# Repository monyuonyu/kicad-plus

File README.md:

**English** | [日本語](README.ja.md) | [简体中文](README.zh-CN.md)

> Translated from [README.ja.md](README.ja.md) (the Japanese version is the original) at commit `fab6b11`.

# kicad-plus — an enhanced KiCad that can work on boards without a GUI

(Formerly **kicad-ja-plus**. The old command names `kicad-local`, `kicad-ja`, `pcbnew-ja` and `eeschema-ja` still work.)

This is KiCad with the additions listed below. It comes in two versions.

| Version | Best for |
|---|---|
| **10.0.6** (recommended) | Based on the latest stable release. Also includes fixes for fabrication output and DRC bugs taken from upstream MRs. **Runs as-is on headless servers, in CI, and from AI agents** |
| 8.0.9 | When you want to keep using your edited files with KiCad 8 |

What was added:

- Tools for working on boards and schematics without opening the GUI (routing, moving footprints, DRC/ERC, 3D images, comparing fabrication output, circuit simulation)
- Features and fixes from KiCad 9–11 and from upstream MRs

**The file format is the same as upstream KiCad of the same version**, so files you edit open as-is in regular KiCad (10 or 8).

## Download

**Latest version: [Releases, Latest](https://github.com/monyuonyu/kicad-plus/releases/latest)** (the recommended 10.0.6 build; the 8.0.9 build that keeps the KiCad 8 format and earlier versions are listed on [Releases](https://github.com/monyuonyu/kicad-plus/releases)).
There are a Windows installer and zip, and a Linux (Ubuntu 24.04) tar.gz; see "Installing" below.

## What it can do

There is a single entry point, `kicad-plus` (`kicad-plus help` lists the commands).

```
kicad-plus drc 基板.kicad_pcb            # DRC summary (count and location per violation type)
kicad-plus erc 回路図.kicad_sch
kicad-plus lint 回路図.kicad_sch          # departures from common design practice (protection on external lines, base resistors, supply capacitors...)
kicad-plus render 基板.kicad_pcb iso      # 3D image without a GUI
kicad-plus render 基板.kicad_pcb top,bottom,iso-hq   # several views in one call (<board>_<view>.png, time per view)
kicad-plus step 基板.kicad_pcb --placeholder-boxes   # STEP; lists parts with no 3D model and substitutes an outline box (height from the Height field)
kicad-plus stats 基板.kicad_pcb           # part count, hole sizes, etc.
kicad-plus netlist 回路図.kicad_sch --json   # netlist as JSON (parts, fields, pin number/name/type, nets and their nodes); for a board, from the pad nets
kicad-plus drc 基板.kicad_pcb --strict    # also the 3 things DRC misses even at "0 violations" (pads without a net, tracks thinner than the netclass, stale zone fills)
kicad-plus why 基板.kicad_pcb             # for each unrouted pair, "why it can't be routed" (keepouts, copper of other nets, board outline), per layer
kicad-plus view 基板.kicad_pcb --drc --net GND   # annotated 2D image (highlighted nets, numbered DRC violations)
kicad-plus autoroute 入力.kicad_pcb 出力.kicad_pcb   # autoroute the whole board with Freerouting, then refill zones and run DRC
kicad-plus finish outline|zone|stitch|islands|widen 入力 出力 ...   # board outline, zones, stitching vias, island removal, widening tracks from current
kicad-plus finish widen 入力 出力 --intent intent.json   # widen every net that has a current in intent.json
kicad-plus ingest 回路図 基板 --out 出力.kicad_pcb --intent intent.json [--place]   # bring in a board made by another tool (Zener etc.): PWR_FLAG, no-connect marks, net names matched to the schematic, netclasses, placement rules, checks (docs/ingest.md)
kicad-plus doctor                        # which commands work here (falls back to the stock KiCad when there is no build)

# Move parts and route (steps can also come from stdin)
kicad-plus route 基板.kicad_pcb 出力.kicad_pcb - --instructions 手順.md <<'EOF'
findspace R10 0.25                  # candidate places where it fits
drag R10 1,0                        # moving it reroutes the connected tracks around it and moves silkscreen text out of the way
autoroute R10.2 C5.1                # automatically find a path with at most 1 via
check                               # DRC on the spot
EOF

kicad-plus sch 入力.kicad_sch 出力.kicad_sch 手順   # edit a schematic without a GUI (after saving: connectivity and BOM diff, ERC)
kicad-plus pcbsync 回路図 基板 出力                # push schematic changes to the board
kicad-plus pcb update-from-schematic --dry-run --json 基板.kicad_pcb   # the same, kicad-cli style; --dry-run only reports changes, a real run ends with a DRC parity check
kicad-plus fabdiff 前.kicad_pcb 後.kicad_pcb 比較/  # compare fabrication output layer by layer, with diff images and a list of locations
kicad-plus sim run 手順.toml --out 結果/            # build SPICE automatically from the schematic and simulate (ngspice)
kicad-plus review 新しい版 前の版 --out 確認/        # ERC, DRC, 3D, diffs and simulation in one run → 報告.md (report)
```

With `--instructions`, it also writes a step-by-step guide that lets a person reproduce the same operations in the KiCad GUI.
**Using it from AI or scripts**: drc, erc, why, view, stats, autoroute, finish and ingest output machine-readable results with `--json`, and drc, erc and why return
exit code 1 when something needs checking (so the next decision can be made from the result without parsing text). The 10.0.6 version runs without a display (DISPLAY).
For details see [docs/guide.md](docs/guide.md), for the tools [tools/README.md](tools/README.md), and for circuit simulation [tools/ksim/README.md](tools/ksim/README.md).

## AI chat in the PCB editor (10.0.6 version)

In the PCB editor, View ("表示") → Panels ("パネル") → AI Chat opens an AI chat panel on the right. You can ask it to look things up or make changes in the open board.

- The AI reads and edits the open board (10.0.6 uses KiCad's IPC API, 8.0.9 uses the Python inside KiCad). **By default, any code that changes the board is shown to you for confirmation every time before it runs**.
  Checking "AI のコードをたずねずに実行する" ("run AI code without asking") at the bottom of the panel skips the confirmation (a warning is shown when you turn it on. It is not saved, so it goes back to asking every time after you close KiCad. The code that was run stays in the chat).
  Changes that were run can be reverted with a single Undo ("元に戻す"), and changes from a run that ended in an error are rolled back.
- DRC and images work by saving a copy of the board and running kicad-cli on it (the open board and its file are not changed).
- It uses **your own Anthropic API key**. You are asked for it the first time, and it is stored in the OS key store (Credential Manager on Windows, etc.).
- **The Windows version and the Linux tar.gz bundle the Python and Claude Agent SDK for the AI** (`<KiCad>/ai-runtime`; `build/ai-runtime` on Linux). No setup or download is needed
  (the conversation with the AI itself needs an Internet connection).
- When built from source, the first time you open it you are asked whether to create a dedicated Python environment (needs Python 3.10 or later and an Internet connection).
  To set it up by hand: `python3 <KiCad の scripting>/kicad_ai/setup_ai.py` (`<KiCad の scripting>` = KiCad's scripting directory).
- If KiCad's API server is stopped, you are asked whether to enable it (the same setting as Preferences ("設定") → Plugins ("プラグイン")).

How it works: the panel (`pcbnew/widgets/panel_ai_chat.cpp`) only shows the conversation and handles approvals; the exchange with the AI is done by a broker in a separate process
(`scripting/kicad_ai/bridge.py`). There are 4 tools: `get_board` (overview and selection), `run_python` (kipy code, with approval), `check` (DRC) and `render` (images).

## Included changes

For each version, the change list gives the source (upstream commit or MR), the adjustments made for that version, and what was verified.

- [10.0.6](patches/10.0.6/README.md): this repository's improvements (headless routing commands, location and layer in DRC JSON, rerouting around moved parts, Gerber comparison, etc.) and **11 upstream MRs** (errors in ODB++ and IPC-2581 fabrication output, variant support in the schematic parity check, a file for `--theme`, etc.)
- [8.0.9](patches/8.0.9/README.md): 00–08 (19 router fixes, features backported from KiCad 9–11, etc.)

No feature that changes the file format is included.

## Installing (Linux, prebuilt)

tar.gz files for Ubuntu 24.04 (x86_64; Ubuntu on WSL2 works too) are on the Releases page for both 10.0.6 and 8.0.9
(`kicad-plus-<version>-linux-x86_64.tar.gz` and `.sha256`).
They contain the improved kicad-cli, the GUI (`kicad`, `pcbnew`, `eeschema` and others), the kifaces, the pcbnew Python module, icons,
translations (Japanese and others), the headless tools, **the Python and Claude Agent SDK for the AI chat (`build/ai-runtime`)**, and **Freerouting with its own Java runtime (`build/freerouting`)**.
Shared components such as wxWidgets, OpenCASCADE and ngspice, and the part libraries and 3D models, come from the upstream KiCad installed on the system.

1. Install upstream KiCad **of the same series** from the PPA

   ```
   sudo add-apt-repository ppa:kicad/kicad-10.0-releases     # for 8.0.9: ppa:kicad/kicad-8.0-releases
   sudo apt install kicad python3-numpy python3-matplotlib python3-pil
   ```

2. Extract it anywhere and add `bin/` to PATH

   ```
   sha256sum -c kicad-plus-10.0.6-linux-x86_64.tar.gz.sha256
   tar xzf kicad-plus-10.0.6-linux-x86_64.tar.gz
   export PATH="$PWD/kicad-plus-10.0.6-linux-x86_64/bin:$PATH"
   kicad-plus help
   kicad-plus-10.0.6-linux-x86_64/package/check-linux.sh   # checks the contents and that things run (tens of seconds)
   kicad-plus test        # regression tests. If everything is OK, the installation is correct
   ```

3. Start the GUI with `pcbnew-plus` (PCB editor), `eeschema-plus` (schematic editor) or `kicad-plus-gui` (project manager)
   (on WSL2 it appears through WSLg). From Python: `kicad-python -c "import pcbnew; print(pcbnew.Version())"`.

- If KiCad has never been started on the system, start `kicad-plus-gui` or upstream `kicad` once to finish the first-run setup (library tables).
- The launchers in `bin/` use the `build/` inside the extracted folder automatically. To use them from another `bin/` (e.g. a git clone of this repository),
  set `export KICAD_LOCAL_BUILD=<extracted folder>/build`.
- If the upstream KiCad is from another series (e.g. the KiCad 8 PPA with the 10.0.6 package), install the missing shared components with
  `sudo apt install $(cat DEPENDS-apt.txt)`. `kicad-plus test` and some tools compare against the system `kicad-cli`, so they fail unless the series match.

For whole-board autorouting (`kicad-plus autoroute`), [Freerouting](https://github.com/freerouting/freerouting) 2.4.1 (GPL-3.0)
and a minimal Java runtime just for it (jlinked from Temurin 25) are bundled (`build/freerouting/`; origin and licenses in its README.txt).
It works on systems without Java. To use another jar or java, set `--jar`, `FREEROUTING_JAR` or `FREEROUTING_JAVA`.
The Windows version has the same in `<KiCad>\freerouting\`, started with `<KiCad>\bin\freerouting.cmd` (Freerouting in the Start menu).
When building from source, provide Java 25 or later and the Freerouting jar yourself (jar location with `--jar` or `FREEROUTING_JAR`).

## Building (Linux)

1. Install the build dependencies (Ubuntu/Debian. The list is in [patches/10.0.6/builddeps.txt](patches/10.0.6/builddeps.txt))

   ```
   sudo apt install $(cat patches/10.0.6/builddeps.txt)     # for 8.0.9: patches/8.0.9/notes/builddeps.txt
   ```

2. Fetch the KiCad source and apply the changes (default location is `~/src/kicad-<version>`)

   ```
   ./apply.sh 10.0.6        # or ./apply.sh 8.0.9
   ```

3. Build (settings verified on Ubuntu 24.04. For 8.0.9, replace 10.0.6 with 8.0.9)

   ```
   cmake -S ~/src/kicad-10.0.6 -B ~/src/build-10.0.6 -G Ninja -DCMAKE_BUILD_TYPE=Release \
         -DKICAD_BUILD_PNS_DEBUG_TOOL=ON -DKICAD_SCRIPTING_WXPYTHON=OFF -DKICAD_BUILD_I18N=OFF
   ninja -C ~/src/build-10.0.6 -j4 kicad-cli pcbnew_kiface eeschema_kiface cvpcb_kiface kicad_route kicad_gerber \
         pcbnew/_pcbnew.so s3d_plugin_vrml s3d_plugin_oce s3d_plugin_idf
   ```

   `KICAD_BUILD_PNS_DEBUG_TOOL=ON` is needed to build kicad_route (`qa/tools/pns/`).
   With 7 GB of memory, up to `-j5` works, and a full build takes about 20–30 minutes. Nothing is installed; it runs from the build directory
   (the entry points in `bin/` set `KICAD_RUN_FROM_BUILD_DIR` and so on).

4. Add `bin/` to PATH (or put the contents of `bin/` in `~/.local/bin`)

   ```
   export PATH="$PWD/bin:$PATH"
   kicad-plus help
   ```

   Set the build directory with `KICAD_LOCAL_BUILD` (default `~/src/build-10.0.6`; for 8.0.9, `export KICAD_LOCAL_BUILD=~/src/build-8.0.9`).
   If you moved the source, set `KICAD_LOCAL_SRC`.
   The part libraries (footprints, symbols, 3D models) come from the upstream KiCad (same series) installed on the system (`/usr/share/kicad`).

## Tests

```
kicad-plus test        # = test/regress.sh (a few tens of seconds)
```

Using the demo board (pic_programmer) and schematic (interf_u) that ship with KiCad 8.0.9, it runs routing steps and compares the results with the baseline (`test/baseline/`),
and also checks each tool individually.

## Folders

| Location | Contents |
|---|---|
| `patches/10.0.6/` | Changes for KiCad 10.0.6 (numbered patches; upstream MRs carry the author's name) |
| `patches/8.0.9/` | Changes for KiCad 8.0.9. `ALL-combined.patch` combines them all; the numbered patches are a historical record |
| `bin/` | Entry points (`kicad-plus`, `kicad-route`, `kicad-gerber`, `kicad-cli-plus`, `kicad-python`) and GUI launchers (`pcbnew-plus`, `eeschema-plus`, `kicad-plus-gui`) |
| `tools/` | Python tools (review, lint, sch, sim, pcbsync, silkfix, ingest, etc.) |
| `adapters/` | Bridges from other board generators to `kicad-plus ingest` (`zener.py`: Zener .zen) |
| `test/` | Regression tests |
| `package/` | Scripts that build the distribution (`linux.sh`: makes a tar.gz from the build directory; `check-linux.sh`: checks an extracted package) |
| `installer/` | Windows installer (NSIS) |
| `docs/guide.md` | Guide (workflow, how to bring in features from the latest version, pitfalls) |

## License

GPL-3.0-or-later (same as KiCad). KiCad itself is by the KiCad developers, and the authors of changes taken from upstream are recorded in each patch.

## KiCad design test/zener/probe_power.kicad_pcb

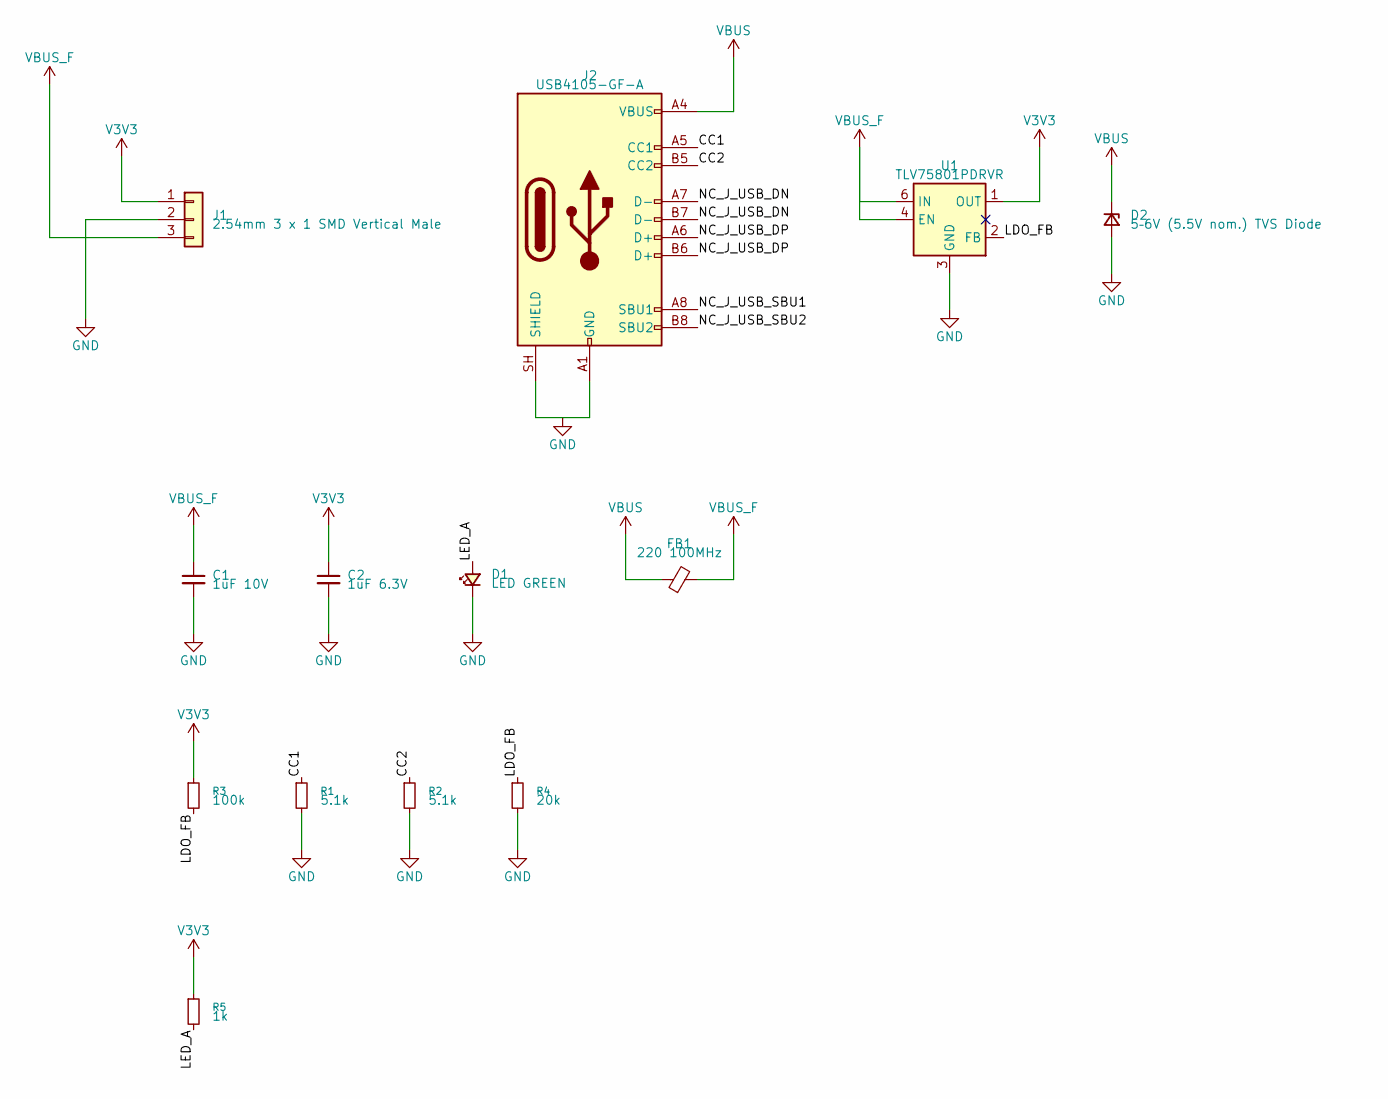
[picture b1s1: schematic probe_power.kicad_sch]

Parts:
C1: 1uF 10V; C_0603_1608Metric
C2: 1uF 6.3V; C_0603_1608Metric
D1: LED GREEN; LED_0603_1608Metric
D2: 5–6V (5.5V nom.) TVS Diode; D_SMF
FB1: 220 100MHz; R_0603_1608Metric
J1: 2.54mm 3 x 1 SMD Vertical Male; PinHeader_1x03_P2.54mm_Vertical_SMD_Pin1Left
J2: USB4105-GF-A; USB_C_Receptacle_GCT_USB4105-xx-A_16P_TopMnt_Horizontal
R1, R2: 5.1k; R_0402_1005Metric
R3: 100k; R_0402_1005Metric
R4: 20k; R_0402_1005Metric
R5: 1k; R_0402_1005Metric
U1: TLV75801PDRVR; WSON-6-1EP_2x2mm_P0.65mm_EP1x1.6mm

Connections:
CC1: J2.A5 (CC1), R1.1
CC2: J2.B5 (CC2), R2.1
GND: C1.2, C2.2, D1.1 (K), D2.2 (A), J1.2, J2.A1 (GND), J2.A12 (GND), J2.B1 (GND), J2.B12 (GND), J2.SH (SHIELD), R1.2, R2.2, R4.2, U1.3 (GND), U1.7 (GND)
LDO_FB: R3.2, R4.1, U1.2 (FB)
LED_A: D1.2 (A), R5.2
NC_J_USB_DN: J2.A7 (D-), J2.B7 (D-)
NC_J_USB_DP: J2.A6 (D+), J2.B6 (D+)
NC_J_USB_SBU1: J2.A8 (SBU1)
NC_J_USB_SBU2: J2.B8 (SBU2)
NC_U_LDO_DNC: U1.5 (DNC)
V3V3: C2.1, J1.1, R3.1, R5.1, U1.1 (OUT)
VBUS: D2.1 (K), FB1.1, J2.A4 (VBUS), J2.A9 (VBUS), J2.B4 (VBUS), J2.B9 (VBUS)
VBUS_F: C1.1, FB1.2, J1.3, U1.4 (EN), U1.6 (IN)

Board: 2 copper layers, 13 parts (0 on the bottom side), 10 nets, no tracks yet.

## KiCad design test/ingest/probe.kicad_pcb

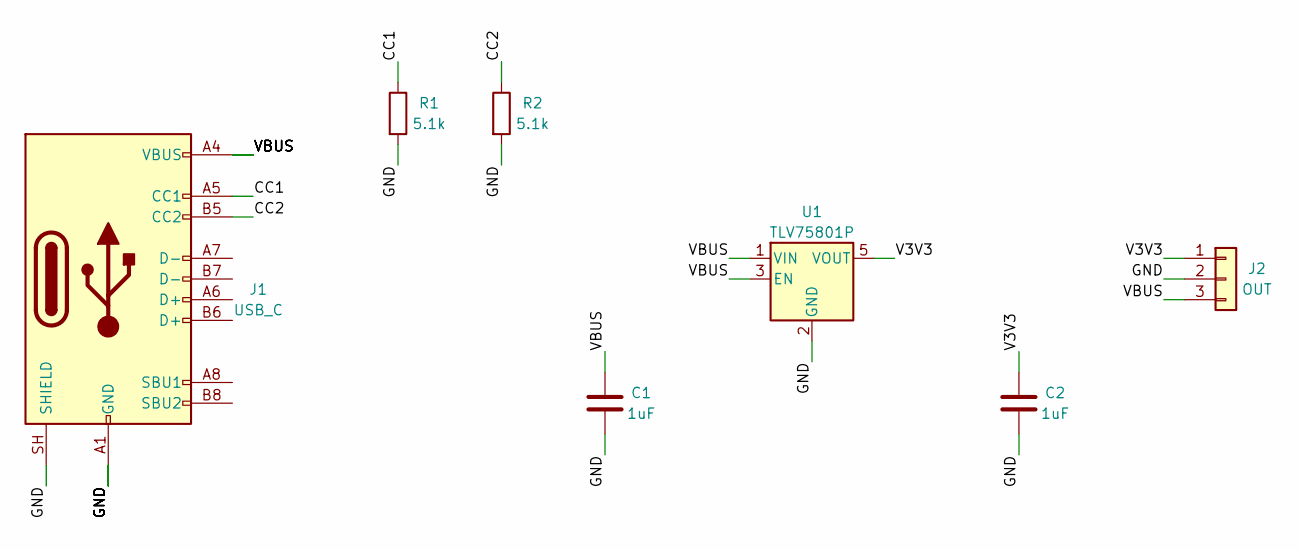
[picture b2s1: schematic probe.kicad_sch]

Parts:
C1, C2: 1uF; C_0603_1608Metric
J1: USB_C; USB_C_Receptacle_GCT_USB4105-xx-A_16P_TopMnt_Horizontal
J2: OUT; PinHeader_1x03_P2.54mm_Vertical
R1, R2: 5.1k; R_0402_1005Metric
U1: TLV75801P; SOT-23-5

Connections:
CC1: J1.A5 (CC1), R1.1
CC2: J1.B5 (CC2), R2.1
GND: C1.2, C2.2, J1.A1 (GND), J1.A12 (GND), J1.B1 (GND), J1.B12 (GND), J1.SH (SHIELD), J2.2, R1.2, R2.2, U1.2 (GND)
NC_J_USB_DNA7: J1.A7 (D-)
NC_J_USB_DNB7: J1.B7 (D-)
NC_J_USB_DPA6: J1.A6 (D+)
NC_J_USB_DPB6: J1.B6 (D+)
NC_J_USB_NC4: U1.4 (NC)
NC_J_USB_SBU1A8: J1.A8 (SBU1)
NC_J_USB_SBU2B8: J1.B8 (SBU2)
V3V3: C2.1, J2.1, U1.5 (VOUT)
VBUS: C1.1, J1.A4 (VBUS), J1.A9 (VBUS), J1.B4 (VBUS), J1.B9 (VBUS), J2.3, U1.1 (VIN), U1.3 (EN)

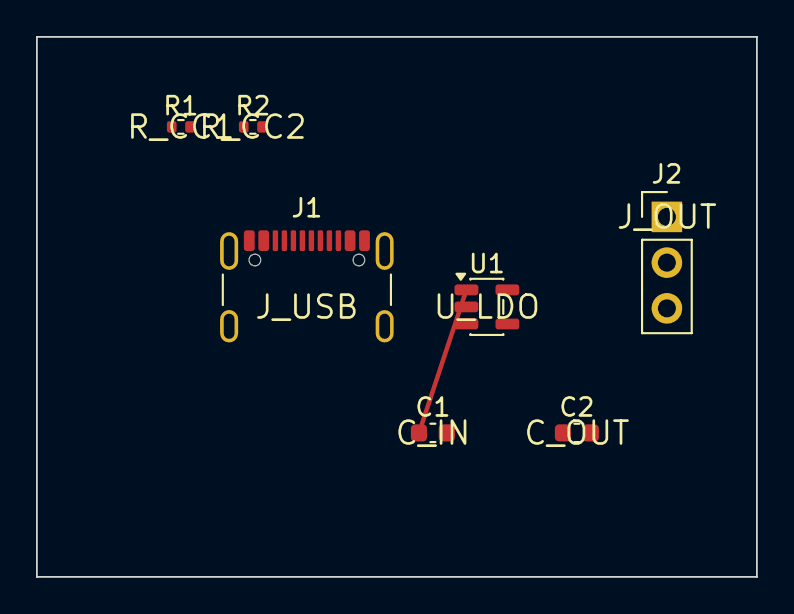
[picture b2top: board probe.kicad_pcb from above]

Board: 2 copper layers, 40.0 x 30.0 mm, 7 parts (0 on the bottom side), 5 nets.
